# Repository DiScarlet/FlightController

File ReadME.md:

# Custom Flight Controller

A custom STM32F405-based flight controller designed from the ground up for modern FPV drones. Supports 4S–6S LiPo batteries, four ESC outputs with DShot, USB-C programming, and the ICM-42688-P IMU. The repository includes complete schematics, PCB design, CAD assembly, hardware documentation, and firmware flashing/bring-up guides. Designed for Betaflight compatibility with future ArduPilot support and additional onboard peripherals.

A preview of the complete assembly by Autodesk Viewer: https://autode.sk/4bVkogq

---

## Documentation

The repository contains additional documentation describing both the hardware and firmware aspects of the project.

Detailed information about the PCB architecture, power distribution, interfaces, mechanical design, manufacturing considerations, and future hardware revisions can be found in **`Docs/Hardware.md`**.

Firmware-related documentation, including programming interfaces, flashing instructions, hardware bring-up, Betaflight target information, and the planned firmware development roadmap, is available in **`Docs/Firmware.md`**.

---

## Repository Structure

FlightController/
├── CAD_Rendered/             # Fusion 360 assembly and mechanical models
├── FCHardware/               # KiCad project files
├── Devlogs/                  # The overall folder with devlog documents
│   ├── Images/                 # Figures and renders
│   └── Journal.md              # Development journal
├── Docs/                     #Documentation
│   ├── Hardware.md         
│   └── Firmware.md
├── ComponentsReferences.csv  # Component purchasing references (BOM)
├── FCHardware.csv            # Design references and documentation
└── README.md

---

## Gallery

### Schematic Overview

### PCB Layout (2D)

### PCB Front (3D)

### PCB Back (3D)

### Fusion 360 Assembly

---

## Acknowledgements

This project would not have been possible without the documentation, manuals, and resources provided by the engineering community. 

Special thanks to:
- STMicroelectronics, TDK InvenSense, Texas Instruments, Diodes Incorporated, Betaflight, Sahil Parashar for providing the generic ESC model that was adapted for this project, KiCad, Autodesk.
- **My family and friends** for their encouragement and support throughout the project.

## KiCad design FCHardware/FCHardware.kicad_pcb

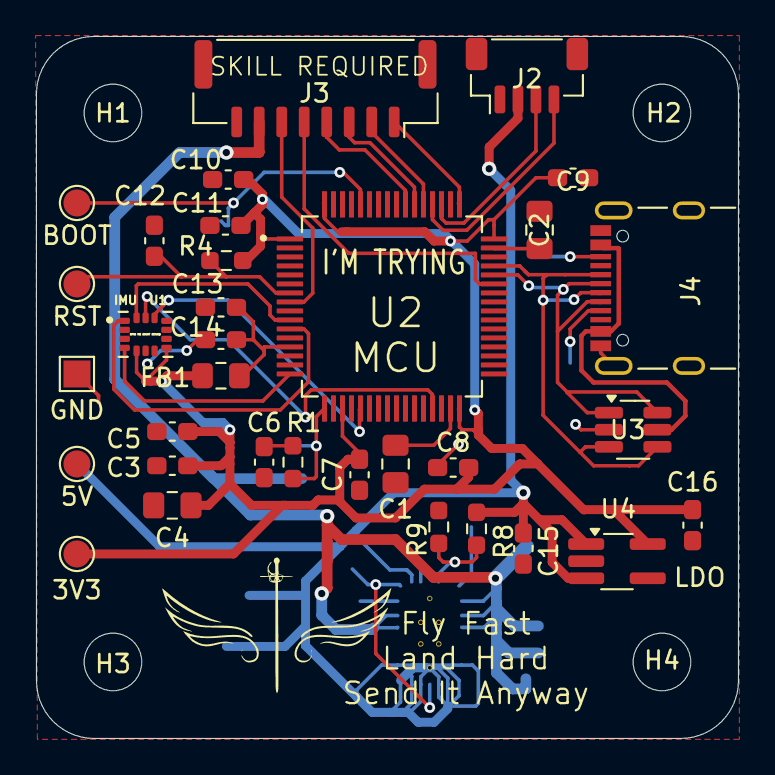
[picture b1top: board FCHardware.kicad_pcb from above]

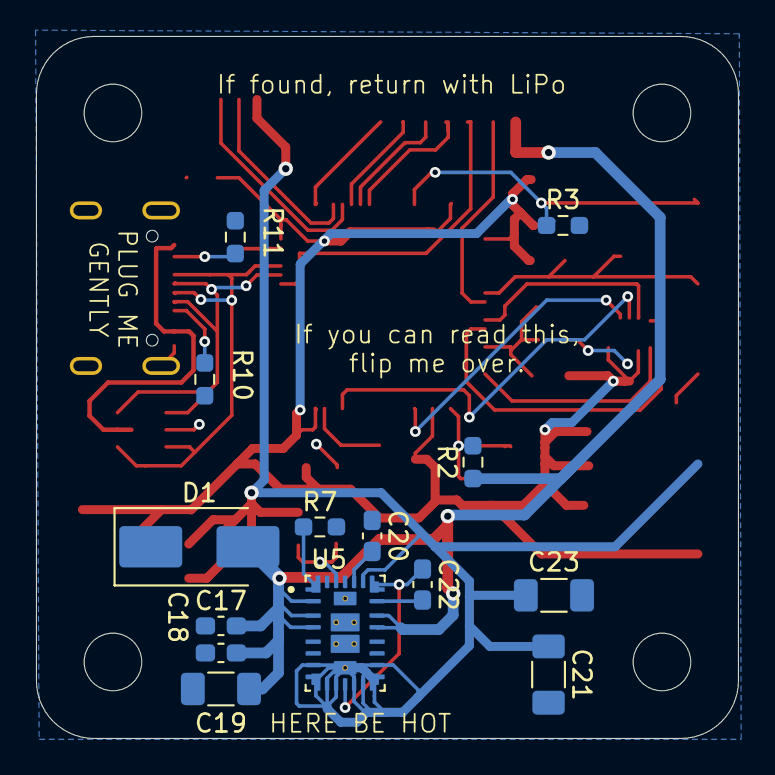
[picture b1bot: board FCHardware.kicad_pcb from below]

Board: 2 copper layers, 39.0 x 39.0 mm, 51 parts (14 on the bottom side), 34 nets.

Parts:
3V3: 3V3TestPoint; TestPoint_Pad_D1.5mm
5V: 5VTestPoint; TestPoint_Pad_D1.5mm
BOOT: BootTestPoint; TestPoint_Pad_D1.5mm
C1, C2, C4: 2u2; C_0805_2012Metric_Pad1.18x1.45mm_HandSolder
C3, C5: 0u1; C_0603_1608Metric_Pad1.08x0.95mm_HandSolder
C6, C7, C8, C9, C10, C11, C12, C18, C22: 100n; C_0603_1608Metric_Pad1.08x0.95mm_HandSolder
C13: 10n; C_0603_1608Metric_Pad1.08x0.95mm_HandSolder
C14, C15, C16, C20: 1u; C_0603_1608Metric_Pad1.08x0.95mm_HandSolder
C17: 680n; C_0603_1608Metric_Pad1.08x0.95mm_HandSolder
C19, C21, C23: 22u; C_1206_3216Metric_Pad1.33x1.80mm_HandSolder
D1: SMBJ28A; D_SMB_Handsoldering
FB1: 1kOhm 100Mhz; L_0805_2012Metric_Pad1.15x1.40mm_HandSolder
GND: GNDTestPoint; TestPoint_Pad_1.5x1.5mm
H1, H2, H3, H4: MountingHole; MountingHole_3.2mm_M3
J2: JST-4pin; JST_SH_BM04B-SRSS-TB_1x04-1MP_P1.00mm_Vertical
J3: JST-8pin; Molex_CLIK-Mate_502386-0870_1x08-1MP_P1.25mm_Horizontal
J4: UJ20-C-H-G-SMT-2A-P16-TR; SAMESKY_UJ20-C-H-G-SMT-2A-P16-TR
R1: 68k; R_0603_1608Metric_Pad0.98x0.95mm_HandSolder
R2: 510k; R_0603_1608Metric_Pad0.98x0.95mm_HandSolder
R3, R4, R9: 10k; R_0603_1608Metric_Pad0.98x0.95mm_HandSolder
R7: 13k; R_0603_1608Metric_Pad0.98x0.95mm_HandSolder
R8: 40.2k; R_0603_1608Metric_Pad0.98x0.95mm_HandSolder
R10, R11: 5k1; R_0603_1608Metric_Pad0.98x0.95mm_HandSolder
RST: ResetTestPoint; TestPoint_Pad_D1.5mm
U1: ICM-42688-P; PQFN50P300X250X97-14N
U2: STM32F405RGTx; QFP50P1200X1200X160-64N
U3: USBLC6-2SC6; SOT-23-6_Handsoldering
U4: AP2112K-3.3; TSOT-23-5_HandSoldering
U5: TPSM63603; CONV_TPSM63603EXTRDHR

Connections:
+3V3: 3V3.1, C3.2, C4.2, C5.1, C7.1, C8.1, C9.1, C10.1, C11.1, C16.2, FB1.1, R4.1, U1.5 (VDDIO), U1.8 (VDD), U2.1 (VBAT), U2.19 (VDD), U2.32 (VDD), U2.48 (VDD), U2.64 (VDD), U4.5 (VOUT)
+5V: 5V.1, C15.1, C21.1, C23.1, J2.2, R8.2, U4.1 (VIN), U4.3 (EN), U5.7 (VOUT), U5.8 (VOUT), U5.9 (VOUT), U5.10 (VOUT), U5.12 (VOUT), U5.13 (VOUT), U5.14 (VOUT), U5.15 (VOUT), U5.22 (VLDOIN), U5.30 (VOUT)
/BOOT0: BOOT.1, R3.1, U2.60 (BOOT0)
/ESC_CRT: J3.6, U2.8 (PC0)
/ESC_TELE: J3.5, U2.43 (PA10)
/IMU_CS: U1.12 (AP_CS), U2.21 (PA5)
/IMU_INT: U1.4 (INT1/INT), U2.16 (PA2)
/IMU_SCLK: U1.13 (AP_SCL/AP_SCLK), U2.29 (PB10)
/IMU_SDI: U1.14 (AP_SDA/AP_SDIO/AP_SDI), U2.10 (PC2)
/IMU_SDO: U1.1 (AP_SDO/AP_AD0), U2.11 (PC3)
/M1: J3.1, U2.49 (PA14)
/M2: J3.2, U2.53 (PC12)
/M3: J3.3, U2.54 (PD2)
/M4: J3.4, U2.55 (PB3)
/NRST: C12.1, R4.2, RST.1, U2.7 (NRST)
/RC_RX: J2.3, U2.51 (PC10)
/RC_TX: J2.4, U2.52 (PC11)
/SW: C22.1, U5.11 (SW), U5.21 (RBOOT)
/USB_D+: J4.A6 (DP1), J4.B6 (DP2), U2.45 (PA12), U3.3 (I/O2), U3.4 (I/O2)
/USB_D-: J4.A7 (DN1), J4.B7 (DN2), U2.44 (PA11), U3.1 (I/O1), U3.6 (I/O1)
/VDD33A: C13.2, C14.2, FB1.2, U2.13 (VDDA)
/V_MON: R1.1, R2.2, U2.17 (PA3)
GND: C1.1, C2.2, C3.1, C4.1, C5.2, C6.1, C7.2, C8.2, C9.2, C10.2, C11.2, C12.2, C13.1, C14.1, C15.2, C16.1, C17.1, C18.1, C19.1, C20.1, C21.2, C23.2, D1.1 (K), GND.1, J2.1, J3.8, J4.A1_B12 (GND), J4.B1_A12 (GND), J4.SH1 (SHIELD), J4.SH2 (SHIELD), J4.SH3 (SHIELD), J4.SH4 (SHIELD), R3.2, R7.1, R9.2, R10.1, R11.1, U1.6 (GND), U1.7 (RESV_7), U2.12 (VSSA), U2.18 (VSS), U2.63 (VSS), U3.2 (GND), U4.2 (GND), U5.5 (PGND), U5.6 (PGND), U5.16 (PGND), U5.17 (PGND), U5.24 (AGND), U5.27 (AGND), U5.28 (PGND), U5.29 (PGND)
unnamed: C6.2, R1.2
unnamed: J4.A5 (CC1), R10.2
unnamed: J4.B5 (CC2), R11.2
unnamed: C1.2, U2.31 (VCAP_1)
unnamed: C2.1, U2.47 (VCAP_2)
unnamed: C22.2, U5.20 (CBOOT)
unnamed: R8.1, R9.1, U5.25 (FB)
unnamed: R7.2, U5.1 (RT)
unnamed: C20.2, U5.23 (VCC)
USB_VBUS: J4.A4_B9 (VBUS), J4.B4_A9 (VBUS), U3.5 (VBUS)
VBAT: C17.2, C18.2, C19.2, D1.2 (A), J3.7, R2.1, U5.2 (EN/SYNC), U5.3 (VIN), U5.4 (VIN), U5.18 (VIN), U5.19 (VIN)
